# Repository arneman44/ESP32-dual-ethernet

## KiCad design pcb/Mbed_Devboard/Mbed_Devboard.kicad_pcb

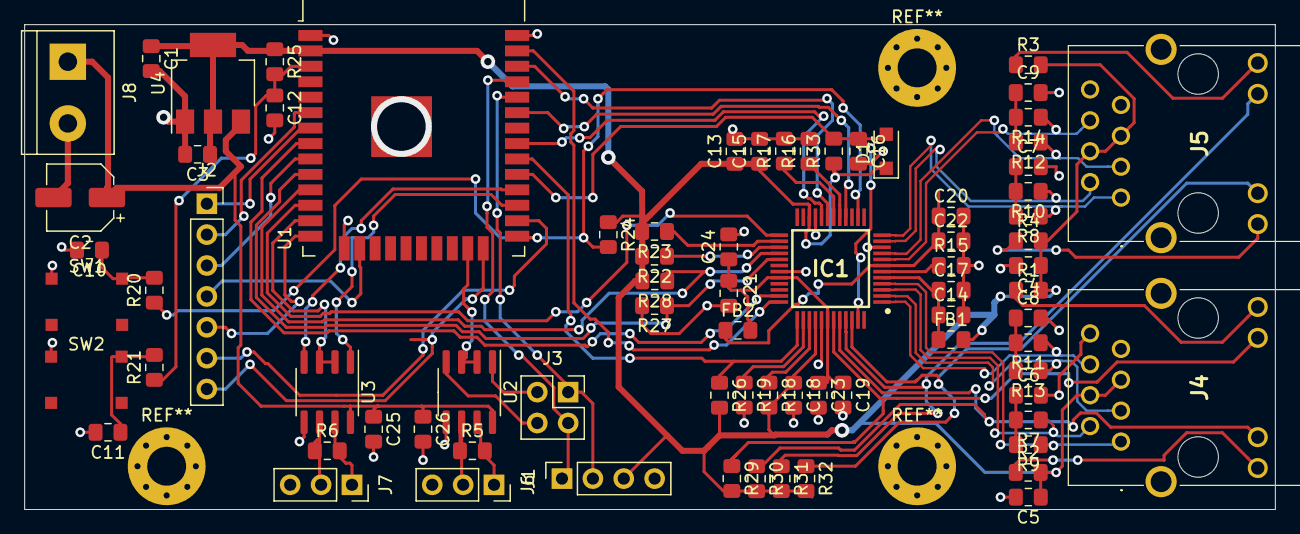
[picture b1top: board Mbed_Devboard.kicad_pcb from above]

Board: 2 copper layers, 102.9 x 39.9 mm, 77 parts (0 on the bottom side), 66 nets.

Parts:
C1, C13, C14, C19, C22: 22uF; C_0805_2012Metric_Pad1.15x1.40mm_HandSolder
C2: 100nF; CP_Elec_5x5.4
C3, C4, C5, C16, C25, C26: 10uF; C_0805_2012Metric_Pad1.15x1.40mm_HandSolder
C6, C7, C8, C9, C15, C17, C18, C21, C23, C24: 0.1uF; C_0805_2012Metric_Pad1.15x1.40mm_HandSolder
C10, C11, C12: 1nF; C_0805_2012Metric_Pad1.15x1.40mm_HandSolder
C20: 0.1uf; C_0805_2012Metric_Pad1.15x1.40mm_HandSolder
D1: SM4007pl; D_SOD-123F
FB1, FB2: Ferrite_Bead; R_0805_2012Metric_Pad1.15x1.40mm_HandSolder
IC1: KSZ8863RLL; QFP50P900X900X160-48N
J1: Conn_01x04; PinSocket_1x04_P2.54mm_Vertical
J2: Conn_01x07; PinSocket_1x07_P2.54mm_Vertical
J3: Conn_02x02_Odd_Even; PinSocket_2x02_P2.54mm_Vertical
J4, J5: HR913550A
J6, J7: Conn_01x03; PinSocket_1x03_P2.54mm_Vertical
J8: Conn_01x02; TerminalBlock_bornier-2_P5.08mm
R1, R2, R3, R4: 50R; R_0805_2012Metric_Pad1.15x1.40mm_HandSolder
R5, R6: 60R; R_0805_2012Metric_Pad1.15x1.40mm_HandSolder
R7, R8, R9, R10, R11, R12, R13, R14: 49.9 1.0%; R_0805_2012Metric_Pad1.15x1.40mm_HandSolder
R15: 11.8R 1.0%; R_0805_2012Metric_Pad1.15x1.40mm_HandSolder
R16, R17, R18, R19, R22, R23, R26, R27, R28, R29, R30, R31, R32, R33: 10K; R_0805_2012Metric_Pad1.15x1.40mm_HandSolder
R20, R21: 470R; R_0805_2012Metric_Pad1.15x1.40mm_HandSolder
R24: 5K; R_0805_2012Metric_Pad1.15x1.40mm_HandSolder
R25: 12k; R_0805_2012Metric_Pad1.15x1.40mm_HandSolder
SW1, SW2: SW_Push; TS5235A
U1: ESP32-WROOM-32D; ESP32-WROOM-32
U2, U3: 75176B; SOIC-8_3.9x4.9mm_P1.27mm
U4: LD1117S33TR_SOT223; SOT-223-3_TabPin2

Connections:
+5V: C2.1, C25.1, C26.1, J8.1, U2.8, U3.8, U4.3
DMX0_en: U1.23, U2.2, U2.3
DMX1_en: U1.13, U3.2, U3.3
EN: C12.1, R21.1, R25.2, U1.3
GND: C1.2, C2.2, C3.2, C4.2, C5.2, C6.2, C7.2, C8.2, C9.2, C10.2, C11.2, C12.2, C13.2, C14.2, C15.2, C16.2, C17.2, C18.2, C19.2, C20.2, C21.2, C22.2, C23.2, C24.2, C25.2, C26.2, IC1.10, IC1.21, IC1.31, IC1.41, J1.4, J4.8, J5.8, J6.3, J7.3, J8.2, R15.2, R16.2, R17.2, R19.2, R27.2, SW1.1, SW2.1, U1.1, U1.15, U1.38, U1.39, U2.5, U3.5, U4.1
IO2: J2.7, U1.24
IO4: J2.6, U1.26
IO12: J2.5, U1.14
IO13: J2.4, U1.16
IO33: J2.3, U1.9
IO34: J2.2, U1.6
IO35: J2.1, U1.7
unnamed: C6.1, R7.2, R9.2
unnamed: C7.1, R8.2, R10.2
unnamed: C8.1, R11.2, R13.2
unnamed: C9.1, R12.2, R14.2
unnamed: C10.1, R20.2, SW1.2
unnamed: C11.1, R21.2, SW2.2
unnamed: IC1.6, R15.1
unnamed: IC1.17, R16.1
unnamed: IC1.18, R17.1
unnamed: IC1.26, R23.1
unnamed: IC1.27, R22.1
unnamed: IC1.38, R19.1
unnamed: IC1.39, R18.1
unnamed: J3.2, U2.1
unnamed: J3.4, U2.4
unnamed: J4.9, R2.1
unnamed: J4.12, R1.1
unnamed: J5.9, R4.1
unnamed: J5.12, R3.1
unnamed: J6.1, R5.2, U2.7
unnamed: J6.2, R5.1, U2.6
unnamed: J7.1, R6.2, U3.7
unnamed: J7.2, R6.1, U3.6
Port1GREEN: IC1.44, J4.10, R30.1
Port1ORANGE: IC1.43, J4.11, R29.1
Port2GREEN: IC1.46, J5.10, R32.1
Port2ORANGE: IC1.45, J5.11, R31.1
RMII_CLK: IC1.14, R20.1, R24.2, U1.25
RMII_CRSDV: IC1.25, U1.12
RMII_INTERR: IC1.35, U1.8
RMII_MDC: IC1.36, U1.37
RMII_MDIO: IC1.37, R26.1, U1.30
RMII_RXD0: IC1.29, R27.1, U1.10
RMII_RXD1: IC1.28, R28.1, U1.11
RMII_TXD0: IC1.20, U1.31
RMII_TXD1: IC1.19, U1.36
RMII_TXEN: IC1.16, U1.33
RX1_N: IC1.1, J4.6, R11.1
RX1_P: IC1.2, J4.3, R13.1
RX2_N: IC1.8, J5.6, R14.1
RX2_P: IC1.9, J5.3, R12.1
Reset_PHY: C16.1, D1.2, IC1.47, R33.2, U1.29
TX1_N: IC1.3, J4.2, R7.1
TX1_P: IC1.4, J4.1, R9.1
TX2_N: IC1.11, J5.2, R10.1
TX2_P: IC1.12, J5.1, R8.1
UART0RX: J1.2, J3.1, U1.34
UART0TX: J1.1, J3.3, U1.35
UART2RX: U1.27, U3.1
UART2TX: U1.28, U3.4
VDDA1.8: C20.1, C22.1, FB2.1, IC1.7
VDDA3.3: C14.1, C17.1, FB1.1, IC1.5
VDDC: C19.1, C21.1, C23.1, C24.1, FB2.2, IC1.32, IC1.42
VDDIO: C1.1, C3.1, C4.1, C5.1, C13.1, C15.1, C18.1, D1.1, FB1.2, IC1.22, IC1.40, J1.3, J4.4, J4.5, J5.4, J5.5, R1.2, R2.2, R3.2, R4.2, R18.2, R22.2, R23.2, R24.1, R25.1, R26.2, R28.2, R29.2, R30.2, R31.2, R32.2, R33.1, U1.2, U4.2

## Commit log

2020-07-08 ESP32 dual Ethernet
